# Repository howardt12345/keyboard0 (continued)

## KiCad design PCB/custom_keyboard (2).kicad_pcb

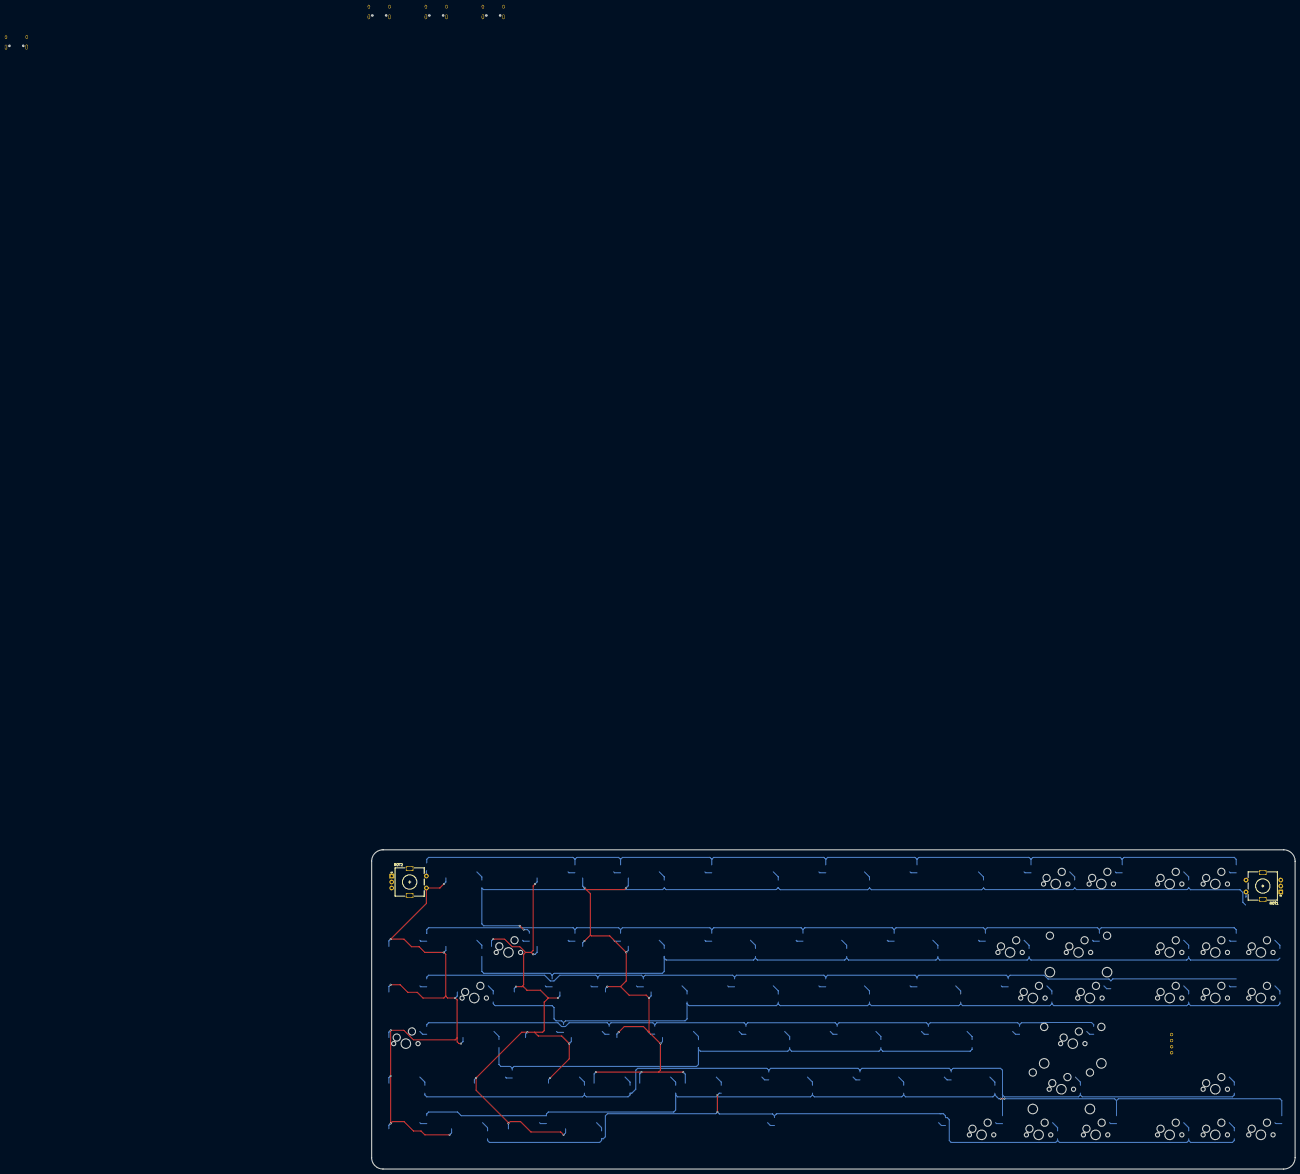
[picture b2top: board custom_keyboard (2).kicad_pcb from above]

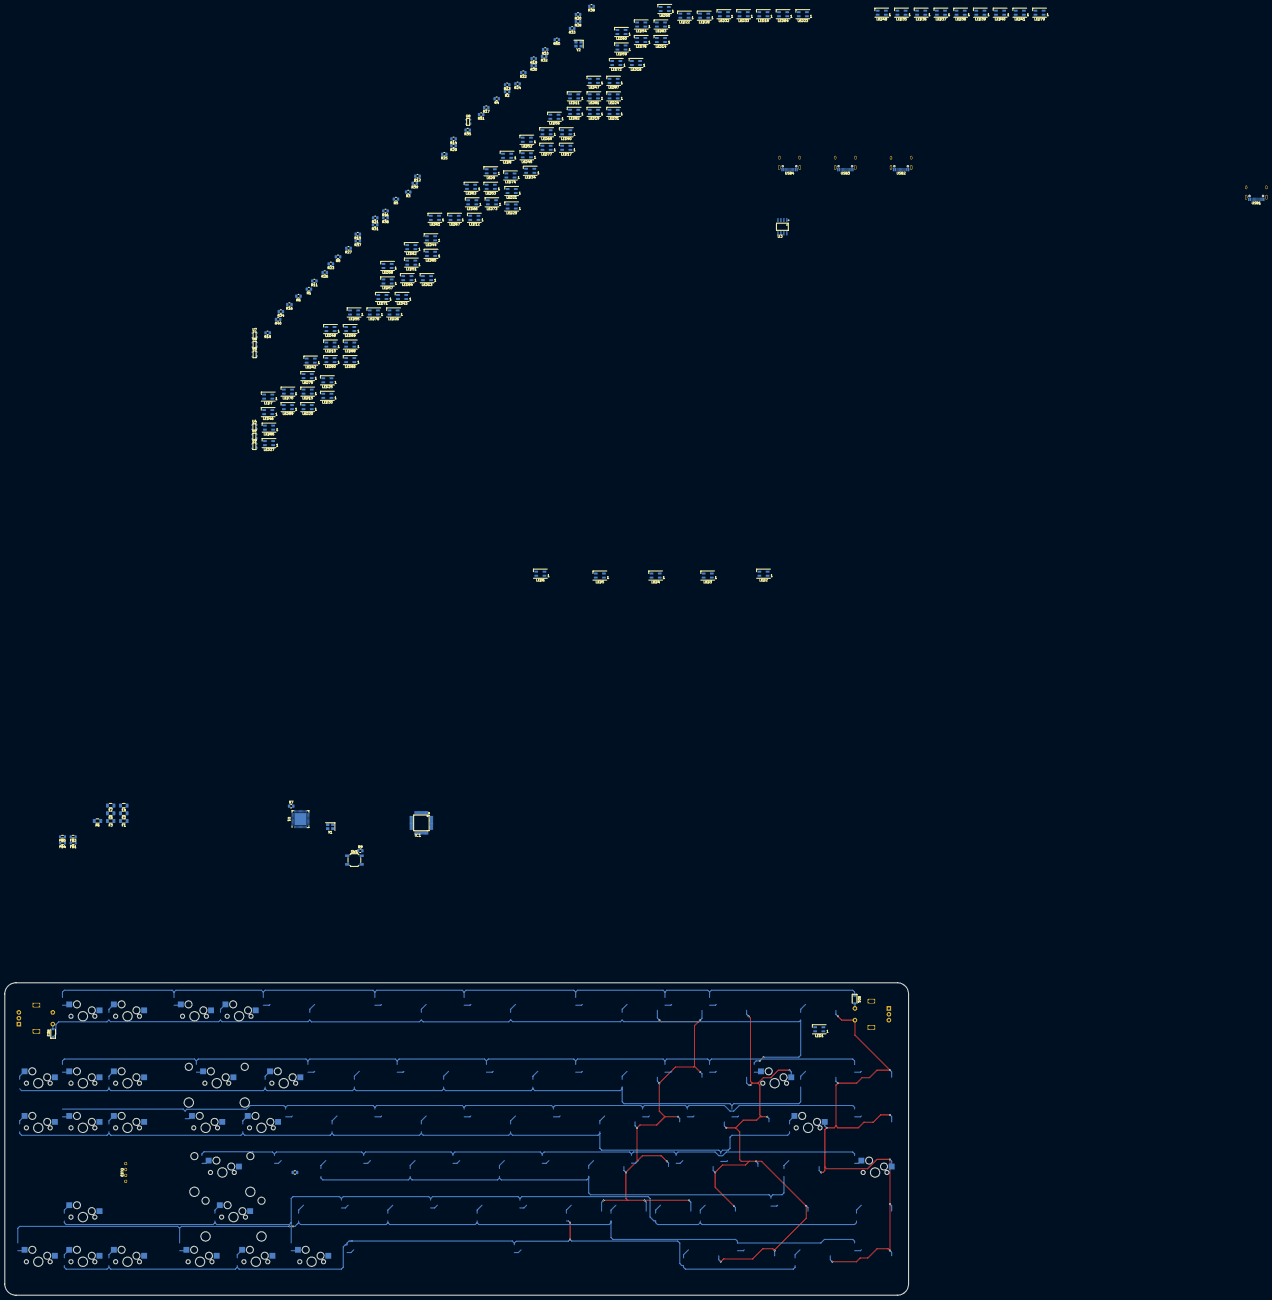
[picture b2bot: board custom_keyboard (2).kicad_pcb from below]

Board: 2 copper layers, 385.7 x 133.3 mm, 193 parts (164 on the bottom side), 171 nets.

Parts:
F1, F2, F3, F4, F5, F6, F7: 500mA; Fuse_1206_3216Metric
FB1, FB3, FB4, FB5: 60 @ 100MHz; L_0805_2012Metric
IC1: FE2.1
LED1, LED2, LED3, LED4, LED5, LED6, LED7, LED8, LED9, LED10, LED11, LED12, LED13, LED14, LED15, LED16, LED17, LED18, LED19, LED20, LED21, LED22, LED23, LED24, LED25, LED26, LED27, LED28, LED29, LED30, LED31, LED32, LED33, LED34, LED35, LED36, LED37, LED38, LED39, LED40, LED41, LED42, LED43, LED44, LED45, LED46, LED47, LED48, LED49, LED50, LED51, LED52, LED53, LED54, LED55, LED56, LED57, LED58, LED59, LED60, LED61, LED62, LED63, LED64, LED65, LED66, LED67, LED68, LED69, LED70, LED71, LED72, LED73, LED74, LED75, LED76, LED77, LED78, LED79, LED80, LED81, LED82, LED83, LED84, LED85, LED86, LED87, LED88, LED89, LED90: WS2812B; LED_SK6812MINI_PLCC4_3.5x3.5mm_P1.75mm
MX3: M3; MXOnly-1U-Hotswap
MX8: TAB; MXOnly-1.5U-Hotswap
MX17: 1; MXOnly-1U-Hotswap
MX68: '/; MXOnly-1U-Hotswap
MX69: RGUI; MXOnly-1.25U-Hotswap
MX70: MENU; MXOnly-1.25U-Hotswap
MX71: F11; MXOnly-1U-Hotswap
MX72: =/+; MXOnly-1U-Hotswap
MX73: ]/}; MXOnly-1U-Hotswap
MX74: RCTRL; MXOnly-1.25U-Hotswap
MX75: F12; MXOnly-1U-Hotswap
MX76: BACKSPACE; MXOnly-2U-Hotswap
MX77: \; MXOnly-1.5U-Hotswap
MX78: ENTER; MXOnly-2.25U-Hotswap
MX79: RSHIFT; MXOnly-2.75U-Hotswap
MX80: LEFT; MXOnly-1U-Hotswap
MX81: PSCR; MXOnly-1U-Hotswap
MX82: INS; MXOnly-1U-Hotswap
MX83: DELETE; MXOnly-1U-Hotswap
MX84: SCLCK; MXOnly-1U-Hotswap
MX85: HOME; MXOnly-1U-Hotswap
MX86: END; MXOnly-1U-Hotswap
MX87: UP; MXOnly-1U-Hotswap
MX88: DOWN; MXOnly-1U-Hotswap
MX89: PGUP; MXOnly-1U-Hotswap
MX90: PGDN; MXOnly-1U-Hotswap
MX91: RIGHT; MXOnly-1U-Hotswap
OL1: OLED; OLED_v2
R1: 500; R_0805_2012Metric
R2, R3, R6, R7, R8, R9, R14: 10k; R_0805_2012Metric
R4, R5, R12, R13, R32, R33, R34, R35, R36, R37, R38, R39, R40, R41, R50, R51: 22; R_0805_2012Metric
R10, R16, R25, R26, R28, R29, R30, R31: 5.1K; R_0805_2012Metric
R11, R15: 100k; R_0805_2012Metric
R17, R18, R19, R20, R21, R22, R23, R24: 330; R_0805_2012Metric
R27: 2.7k; R_0805_2012Metric
RD1, RD2: SOD-123; D_SOD-123
ROT1, ROT2: Rotary_Encoder_Switch; RotaryEncoder_Alps_EC11E-Switch_Vertical_H20mm
SW1: SW_Push; SW_SPST_SKQG_WithStem
U1: ATmega32U4-MU; QFN-44-1EP_7x7mm_P0.5mm_EP5.2x5.2mm
U2, U4, U5, U6, U7, U8, U9: PRTR5V0U2X; SOT143B
U3: 24LC02; 24LC04
USB1, USB2, USB3, USB4: HRO-TYPE-C-31-M-12; HRO-TYPE-C-31-M-12-Assembly
Y1: 16MHz; Crystal_SMD_3225-4Pin_3.2x2.5mm
Y2: 12MHz; Crystal_SMD_3225-4Pin_3.2x2.5mm

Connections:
+1V8: IC1.6, IC1.21, IC1.25, IC1.28
+3V3: IC1.9, IC1.15, IC1.20, IC1.26, IC1.31, IC1.36, IC1.42, IC1.43, IC1.45, R11.1, U3.7, U3.8
+5V: F1.1, F2.1, F3.1, F4.1, F5.1, F6.1, F7.1, IC1.8, LED1.1, LED2.1, LED3.1, LED4.1, LED5.1, LED6.1, LED7.1, LED8.1, LED9.1, LED10.1, LED11.1, LED12.1, LED13.1, LED14.1, LED15.1, LED16.1, LED17.1, LED18.1, LED19.1, LED20.1, LED21.1, LED22.1, LED23.1, LED24.1, LED25.1, LED26.1, LED27.1, LED28.1, LED29.1, LED30.1, LED31.1, LED32.1, LED33.1, LED34.1, LED35.1, LED36.1, LED37.1, LED38.1, LED39.1, LED40.1, LED41.1, LED42.1, LED43.1, LED44.1, LED45.1, LED46.1, LED47.1, LED48.1, LED49.1, LED50.1, LED51.1, LED52.1, LED53.1, LED54.1, LED55.1, LED56.1, LED57.1, LED58.1, LED59.1, LED60.1, LED61.1, LED62.1, LED63.1, LED64.1, LED65.1, LED66.1, LED67.1, LED68.1, LED69.1, LED70.1, LED71.1, LED72.1, LED73.1, LED74.1, LED75.1, LED76.1, LED77.1, LED78.1, LED79.1, LED80.1, LED81.1, LED82.1, LED83.1, LED84.1, LED85.1, LED86.1, LED87.1, LED88.1, LED89.1, LED90.1, MX68.1, OL1.3, R9.1, R14.1, U1.2, U1.7, U1.14, U1.24, U1.34, U1.44
BKL_DATA_IN: R1.2, U1.1
COL0: MX3.1, MX8.1, ROT2.S1, U1.8
COL1: MX17.1, U1.9
COL6: MX69.1, MX70.1, MX71.1, MX72.1, MX73.1, MX74.1, U1.21
COL7: MX75.1, MX76.1, MX77.1, MX78.1, MX79.1, MX80.1, MX81.1, MX82.1, MX83.1, U1.22
COL8: MX84.1, MX85.1, MX86.1, MX87.1, MX88.1, MX89.1, MX90.1, MX91.1, ROT1.S1, U1.25
DOUT1: LED2.2, LED82.4
DOUT2: LED3.2, LED83.4
DOUT3: LED4.2, LED84.4
DOUT4: LED5.2, LED85.4
DOUT5: LED6.2, LED86.4
DOUT6: LED7.2, LED87.4
DOUT7: LED8.2, LED88.4
DOUT8: LED9.2, LED89.4
ENCODER_A: R2.2, R6.2
ENCODER_B1: R3.1, R8.1, U1.40
Earth: FB1.1, FB3.1, FB4.2, FB5.2, USB1.13, USB2.13, USB3.13, USB4.13
GND: FB1.2, FB3.2, FB4.1, FB5.1, IC1.10, IC1.24, IC1.39, LED1.3, LED2.3, LED3.3, LED4.3, LED5.3, LED6.3, LED7.3, LED8.3, LED9.3, LED10.3, LED11.3, LED12.3, LED13.3, LED14.3, LED15.3, LED16.3, LED17.3, LED18.3, LED19.3, LED20.3, LED21.3, LED22.3, LED23.3, LED24.3, LED25.3, LED26.3, LED27.3, LED28.3, LED29.3, LED30.3, LED31.3, LED32.3, LED33.3, LED34.3, LED35.3, LED36.3, LED37.3, LED38.3, LED39.3, LED40.3, LED41.3, LED42.3, LED43.3, LED44.3, LED45.3, LED46.3, LED47.3, LED48.3, LED49.3, LED50.3, LED51.3, LED52.3, LED53.3, LED54.3, LED55.3, LED56.3, LED57.3, LED58.3, LED59.3, LED60.3, LED61.3, LED62.3, LED63.3, LED64.3, LED65.3, LED66.3, LED67.3, LED68.3, LED69.3, LED70.3, LED71.3, LED72.3, LED73.3, LED74.3, LED75.3, LED76.3, LED77.3, LED78.3, LED79.3, LED80.3, LED81.3, LED82.3, LED83.3, LED84.3, LED85.3, LED86.3, LED87.3, LED88.3, LED89.3, LED90.3, MX68.2, OL1.4, R7.1, R10.1, R15.2, R16.1, R24.1, R25.1, R26.1, R27.1, R28.1, R29.1, R30.1, R31.1, ROT1.C, ROT2.C, SW1.2, U1.5, U1.15, U1.23, U1.35, U1.43, U1.45, U2.1, U3.1, U3.2, U3.3, U3.4, U4.1, U5.1, U6.1, U7.1, U8.1, U9.1, USB1.1, USB1.12, USB2.1, USB2.12, USB3.1, USB3.12, USB4.1, USB4.12, Y1.2, Y1.4, Y2.2, Y2.4
HUB_D+: IC1.30, R12.2
HUB_D-: IC1.29, R13.2
HUB_LED1: IC1.3, R17.2, U3.6
HUB_LED2: IC1.4, R18.2
HUB_LED3: IC1.5, R19.2
HUB_LED4: IC1.7, R20.2
HUB_LED5: IC1.48, R21.2
HUB_LED6: IC1.47, R22.2
HUB_LED7: IC1.46, R23.2
HUB_PORT2_D+: IC1.17, R38.2
HUB_PORT2_D-: IC1.16, R39.2
HUB_PORT3_D+: IC1.14, R40.2
HUB_PORT3_D-: IC1.13, R41.2
HUB_PORT4_D+: IC1.12, R50.2
HUB_PORT4_D-: IC1.11, R51.2
HUB_PORT5_D+: IC1.33, R33.2
HUB_PORT5_D-: IC1.32, R32.2
HUB_PORT6_D+: IC1.35, R35.2
HUB_PORT6_D-: IC1.34, R34.2
HUB_PORT7_D+: IC1.38, R37.2
HUB_PORT7_D-: IC1.37, R36.2
HUB_SDA: IC1.2, U3.5
HUB_XIN: IC1.22, Y2.1
HUB_XOUT: IC1.23, Y2.3
KEYBOARD_D+: IC1.19, R4.1
KEYBOARD_D-: IC1.18, R5.2
KEYBOARD_RESET: R9.2, SW1.1, U1.13
KEYBOARD_SCL: OL1.1, U1.18
KEYBOARD_SDA: OL1.2, U1.19
KEYBOARD_XTAL1: U1.17, Y1.1
KEYBOARD_XTAL2: U1.16, Y1.3
unnamed: R2.1, ROT2.A
unnamed: R3.2, ROT2.B
unnamed: R6.1, ROT1.A
unnamed: R8.2, ROT1.B
unnamed: IC1.27, R27.2
unnamed: R39.1, U4.3
unnamed: R38.1, U4.2
unnamed: R41.1, U5.3
unnamed: R40.1, U5.2
unnamed: R51.1, U6.3
unnamed: R50.1, U6.2
unnamed: LED1.2, R1.1
unnamed: LED1.4, LED10.2
unnamed: LED10.4, LED19.2
unnamed: LED2.4, LED11.2
unnamed: LED11.4, LED20.2
unnamed: LED3.4, LED12.2
unnamed: LED12.4, LED21.2
unnamed: LED4.4, LED13.2
unnamed: LED13.4, LED22.2
unnamed: LED5.4, LED14.2
unnamed: LED14.4, LED23.2
unnamed: LED6.4, LED15.2
unnamed: LED15.4, LED24.2
unnamed: LED7.4, LED16.2
unnamed: LED16.4, LED25.2
unnamed: LED8.4, LED17.2
unnamed: LED17.4, LED26.2
unnamed: LED9.4, LED18.2
unnamed: LED18.4, LED27.2
unnamed: LED19.4, LED28.2
unnamed: LED20.4, LED29.2
unnamed: LED21.4, LED30.2
unnamed: LED22.4, LED31.2
unnamed: LED23.4, LED32.2
unnamed: LED24.4, LED33.2
unnamed: LED25.4, LED34.2
unnamed: LED26.4, LED35.2
unnamed: LED27.4, LED36.2
unnamed: LED28.4, LED37.2
unnamed: LED29.4, LED38.2
unnamed: LED30.4, LED39.2
unnamed: LED31.4, LED40.2
unnamed: LED32.4, LED41.2
unnamed: LED33.4, LED42.2
unnamed: LED34.4, LED43.2
unnamed: LED35.4, LED44.2
unnamed: LED36.4, LED45.2
unnamed: LED37.4, LED46.2
unnamed: LED38.4, LED47.2
unnamed: LED39.4, LED48.2
unnamed: LED40.4, LED49.2
unnamed: LED41.4, LED50.2
unnamed: LED42.4, LED51.2
unnamed: LED43.4, LED52.2
unnamed: LED44.4, LED53.2
unnamed: LED45.4, LED54.2
unnamed: LED46.4, LED55.2
unnamed: LED47.4, LED56.2
unnamed: LED48.4, LED57.2
unnamed: LED49.4, LED58.2
unnamed: LED50.4, LED59.2
unnamed: LED51.4, LED60.2
unnamed: LED52.4, LED61.2
unnamed: LED53.4, LED62.2
unnamed: LED54.4, LED63.2
unnamed: LED55.4, LED64.2
unnamed: LED56.4, LED65.2
unnamed: LED57.4, LED66.2
unnamed: LED58.4, LED67.2
unnamed: LED59.4, LED68.2
unnamed: LED60.4, LED69.2
unnamed: LED61.4, LED70.2
unnamed: LED62.4, LED71.2
unnamed: LED63.4, LED72.2
unnamed: LED64.4, LED73.2
unnamed: LED65.4, LED74.2
unnamed: LED66.4, LED75.2
unnamed: LED67.4, LED76.2
unnamed: LED68.4, LED77.2
unnamed: LED69.4, LED78.2
unnamed: LED70.4, LED79.2
unnamed: LED71.4, LED80.2
unnamed: LED72.4, LED81.2
unnamed: LED73.4, LED82.2
unnamed: LED74.4, LED83.2
unnamed: LED75.4, LED84.2
unnamed: LED76.4, LED85.2
unnamed: LED77.4, LED86.2
unnamed: LED78.4, LED87.2
unnamed: LED79.4, LED88.2
unnamed: LED80.4, LED89.2
unnamed: LED81.4, LED90.2
unnamed: R4.2, U1.4
unnamed: R5.1, U1.3
unnamed: R7.2, U1.33
unnamed: R10.2, USB2.10
unnamed: R12.1, U2.2, USB1.6
unnamed: R13.1, U2.3, USB1.5, USB1.7, USB1.8
unnamed: R16.2, USB3.10
unnamed: R25.2, USB1.10
unnamed: R26.2, USB1.4
unnamed: R28.2, USB4.10
unnamed: R29.2, USB2.4
unnamed: R30.2, USB3.4
unnamed: R31.2, USB4.4
unnamed: R32.1, U7.3, USB2.5, USB2.7, USB2.8
unnamed: R33.1, U7.2, USB2.6
unnamed: R34.1, U8.3, USB3.5, USB3.7, USB3.8
unnamed: R35.1, U8.2, USB3.6
unnamed: R36.1, U9.3, USB4.5, USB4.7, USB4.8
unnamed: R37.1, U9.2, USB4.6
unnamed: RD1.2, ROT2.S2
unnamed: RD2.2, ROT1.S2
ROT1_ROW: RD2.1, U1.38, U1.41
ROT2_ROW: RD1.1, U1.39
VBUSM: IC1.41, R14.2, R15.1
VCC: F1.2, F2.2, F3.2, F4.2, F5.2, F6.2, F7.2, U2.4, U4.4, U5.4, U6.4, U7.4, U8.4, U9.4, USB1.2, USB1.11, USB2.2, USB2.11, USB3.2, USB3.11, USB4.2, USB4.11
XRSTJ: IC1.40, R11.2

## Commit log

2021-09-25 Add submodules
2021-09-25 Added libraries
2021-09-26 Setting up microcontroller pin layout
2021-09-26 Keyboard controller sections
2021-09-26 Keyboard matrix
2021-09-26 RGB LED Matrix
2021-09-26 Added outlines
2021-09-27 Corrected most electrical rules checks
2021-09-27 Keyboard OLED label
2021-09-27 Imported FE2.1
2021-09-27 Removed unnecessary lighting
2021-09-28 USB Hub Setup
2021-09-28 USB hub connections
2021-09-28 Reannotated components
2021-09-28 USB Hub sections
2021-09-28 Adjusted section outlines
2021-09-28 Alternate schematic
2021-09-29 Assigned footprints to alternate schematic
2021-09-29 Set up PCB
2021-09-29 Positioned key diodes
2021-09-29 Placed resistors and capacitators
2021-09-30 Halfway done USB ports
2021-09-30 Routed lights
2021-09-30 Rows routed
2021-10-01 Organized USB Hub location
2021-10-01 Connected controller to columns
2021-10-01 LED routing
2021-10-01 Routed some of the USB lanes
2021-10-01 Copied to another file
2021-10-01 LEDs routed, removed 1 USB port
2021-10-01 Moved USB hub to top, made top gap 0.5u
2021-10-01 Connected all USB ports to hub
2021-10-02 State before deleting all traces
2021-10-02 Copy with duplex matrix
2021-10-02 Relabeled keyboard and LED matrix
2021-10-04 Updated USB hub schematic
2021-10-05 Creating copy to use with STM32
2021-10-05 replaced controller with ATMEGA32U4
2021-10-05 better USB circuitry
2021-10-06 Assigned footprints to symbols
2021-10-06 MX keys positioned
2021-10-06 Updated footprints
2021-10-06 Keyboard diodes in place
2021-10-06 Routed rows and some columns
2021-10-06 Converted to STM32F303
2021-10-07 Reannotated the keyboard and LED matrices
2021-10-07 Created pcb and mapped keyboard matrix
2021-10-08 Remapped keyboard rows
2021-10-08 Placed some of the LEDs
2021-10-08 New version with combined footprint
2021-10-08 Placed LED capacitators
2021-10-08 Routed everything regarding the USB hub
2021-10-08 Connected 5V to USB hub
2021-10-09 Connected LED rows
2021-10-09 Placed microcontroller components in position
2021-10-09 Added mounting holes
2021-10-09 Mapped rows to microcontroller
2021-10-09 Mapped columns to microcontroller
2021-10-09 Routed Rotary Encoders
2021-10-09 Fixed row routing
2021-10-09 Moved previous drafts to archive
2021-10-10 Made various adjustments
2021-10-11 Finished first draft
2021-10-11 Gerber files for the first draft
2021-10-12 Draft 1-1 with different components
2021-10-12 Saved project
2021-10-12 Routed GND to crystal
2021-10-12 Renamed files
2021-10-12 Cheaper component
2021-10-17 Made tweaks to layout
2021-10-17 Created keyboard plate
2021-10-17 Tweak to footprints
2021-10-19 Drew outlines for case
2021-10-19 Draft files
2021-10-19 Moved microcontroller and side USBs
2021-10-19 Connected earth
2021-10-20 Made some traces shorter
2021-10-20 Tidied up some traces
2021-10-20 Draft 1-2
2021-10-21 Added a ferrite bead
2021-10-21 Updated gerber files for draft 1-2
2021-10-22 Updated files, prepped for review
2021-10-22 Removed unused draft
2021-10-22 Gerber files for draft 1-2
2021-10-23 Added pullup resistors for oled
2021-10-23 Added pullups to EEPROM
2021-10-23 Moved USB ports out by a bit
2021-10-24 Added power control to downstream ports
2021-10-24 Updated PCB from schematic
2021-10-24 Exported gerber files for draft 1-3
2021-10-24 Fixed JLCPCB BOM file not generating
2021-10-24 Disconnected shield nets from each other
2021-10-25 Addressed several issues with power
    - Rearranged downstream ports so that the fuse is positioned better
    - Added ferrite beads to downstream ports
    - Added fuse to LED matrix
2021-10-25 Screenshots for 2021-10-24
2021-10-25 Rearranged vias
2021-10-25 Schematic screenshot
2021-10-25 Cleaned up traces and fill
2021-10-26 Added testpoints to microcontroller
2021-10-26 connected microcontroller testpoints in PCB
2021-10-26 Added fuse to LED matrix
2021-10-26 Added JLCPCB Part numbers
2021-10-27 Minor adjustments to schematic and pcb
2021-10-27 Exported draft for 2021-10-26 for review and cost check
2021-10-27 Removed pullup resistors on rotary encoders
2021-10-28 Reassigned pins on microcontroller
    - they were all completely incorrect
2021-10-28 Gerber files as of 2021-10-27
2021-10-29 Removed old plate project
2021-10-29 Adapted schematic and PCB for F103
2021-10-30 Changed USB test pads to pad style, moved resistors
2021-11-01 Changed reset circuit
2021-11-01 Rearranged components on schematic
2021-11-01 Changes to F303 schematic and PCB before switch to F103
2021-11-01 Tidied up components on schematic and PCB
2021-11-02 Added logo, copyright, and credits
2021-11-02 init firmware project
2021-11-02 Moved resistors closer to usb hub ic
2021-11-03 Added indicator LEDs to keyboard power
2021-11-03 Added guard traces, double checked part numbers
2021-11-03 Double checked traces
2021-11-03 Renamed test points, fixed DRC errors
2021-11-03 Tweaked label locations
2021-11-03 Exported gerber files
2021-11-03 Exported keyboard plate files
2021-11-04 Removed open load detect resistors
2021-11-04 Preliminary QMK firmware
2021-11-04 Added rotary encoder support
2021-11-05 Draft 1-5 with MCU swapped with F303
2021-11-05 Slightly adjusted USB traces
2021-11-05 Created copy with F303, restored original to F103
2021-11-05 Exported production files for draft 1-5
2021-11-06 Exported files for first prototype
2021-11-06 Exported plate files for ordering
2021-11-09 Reorganized PCB files
2021-11-09 (not in 1st proto) Fixed rotary encoder locations
2021-11-09 Created copy of revision
2021-11-24 Halfway through converting to FE1.1s
2021-11-27 2nd prototype
2021-11-27 Updated readme with documentation on 1st prototype
2021-11-29 Changed ESD protection IC
2021-12-01 Added indicator LED
2021-12-01 Removed encoder resistors and capacitors
2021-12-04 Daisy chain routed diodes
2021-12-04 Reassigned PC13/14/15
2021-12-05 Moved traces over by 1 gridline
2021-12-05 Saving before exporting for review
2021-12-06 Adding IS31FL3731 RGB matrix
2021-12-06 Gerber export and pics for review
2021-12-06 Replaced keyboard matrix schematic
2021-12-06 Fixed issues with matrix
2021-12-06 Separated LED footprints into groups
2021-12-07 Removed IS31FL3731 RGB matrix
2021-12-09 Adjusted component part numbers
2021-12-09 Replaced KEYBOARD_5V with VCC
2021-12-09 Test SVG
2021-12-09 Figuring out LED positions
2021-12-09 Changed KEYBOARD_5V to VCC
2021-12-10 Exported gerber
2021-12-12 v2 plate
2021-12-13 Footprint for MHT151RGBCT
2021-12-13 Removed mounting holes
2021-12-14 Changed JST and button compoent
2021-12-14 Modified outline
2021-12-15 Replaced footprints
2021-12-15 Centered text
2021-12-16 Routed LEDs on 1CA
2021-12-17 Routed LEDs on 1CB
2021-12-18 Connected I1 to MCU
2021-12-18 Placed rest of LEDs onto board
2021-12-18 Exported to get estimate
2021-12-18 Routed LEDs on 2CA
2021-12-18 Routed LEDs on 2CB
2021-12-19 Routed LEDs on I3
2021-12-20 Gave JST connector its own fuse and ferrite bead
2021-12-20 Tweaked routing and footprints
2021-12-20 Exported gerbers
2021-12-21 Exported for review
2021-12-23 EVQWGD001 footprint
2021-12-23 Tweaked indicator LED circuit
2021-12-23 Removed 22ohm resistors
2021-12-23 Added the Kailh hotswap socket 3d model
    from https://github.com/qmk/qmk_hardware/tree/master/components
2021-12-23 Made slight tweaks to USB layout
2021-12-23 Added SM04B-SRSS-TB-LF-SN model
2021-12-24 Exported gerbers for 2nd prototype manufacturing
2021-12-25 Mirrored XCB blocks on Y axis on RGB matrix
2021-12-25 Plate v2
2021-12-28 Archived prototype 2
2021-12-29 Set origin point
2022-01-01 BOM with quantity for LCSC ordering
2022-01-03 Added measurements
2022-01-06 Rename: custom_keyboard (f303) -> keyboard0
2022-01-06 Removed archive folder
2022-01-06 Removed unnecessary submodule
2022-01-06 Updated prototype 1 readme
2022-01-06 Updated readme and added cc-by-nc-sa license
2022-01-06 2nd prototype readme
2022-01-08 Adjusted OLED cutout
2022-01-09 Added a lot of flex cuts
2022-01-17 Exported plate v2 for production
2022-01-17 Swapped photo
2022-01-21 slight adjustments to plate v2
2022-01-21 Added USB C model
2022-02-01 refractored to match new version designations
2022-02-01 Upgraded to Kicad 6
2022-02-02 Switched RGB lighting to SK6812s
2022-02-02 moved label
2022-02-02 SK6812 3d model
2022-02-06 Swapped switch footprints with anti shear footprints
2022-02-06 connected LEDs
2022-02-07 backlight assigned to A9
2022-02-20 Top facing space stabilizerr
2022-02-20 Adjusted traces
2022-02-21 Reassigned bottom rows (no longer compatible with p2)
2022-02-21 Flipped enter stabilizer
2022-02-21 Moved A9 text to B2
2022-02-21 Added screw holes to plate v2
2022-02-21 renamed to p3
2022-02-23 Additional documentation
2022-02-23 Link spacing
2022-03-05 Added EVQWD001, exported for production
2022-03-05 v3 plate and bottom plate
2022-03-05 Adjusted text and graphics widths
2022-03-05 created foot and exported for production
2022-03-06 fixed tolerances
2022-03-06 Tainan SVG
2022-03-06 map variant of bottom plate
2022-03-06 Fixed map variant issues
2022-03-06 renamed to keyboard0 - SK6812
2022-03-06 Toronto map on plate
2022-03-06 Adjusted alignment of map
2022-03-06 keyboard0 p2 rev 2 (2.1)
    - Changed hotswaps to antishear
    - Added ESD onto JST
    - USB footprint to default footprint
    - Added EVQWGD001
    - Force stepped caps
    - Rotated some stabilizers
2022-03-06 Exported for production
2022-03-08 Final verification before ordering
2022-03-08 Culled parts of silkscreen outside outline
2022-03-09 Revised maps silkscreen
2022-03-12 Exported files for additional quotation
2022-03-12 Case files
2022-03-12 3d print parts
2022-03-12 moved p2.1 folder
2022-03-12 Cleaned up plate v3 files
2022-03-12 Renamed folder
2022-03-12 Added readme and renders
2022-03-13 Fixed overlapping lines
2022-03-13 Combined 3d part
2022-03-13 Readme and diagram
2022-03-13 Added another render
